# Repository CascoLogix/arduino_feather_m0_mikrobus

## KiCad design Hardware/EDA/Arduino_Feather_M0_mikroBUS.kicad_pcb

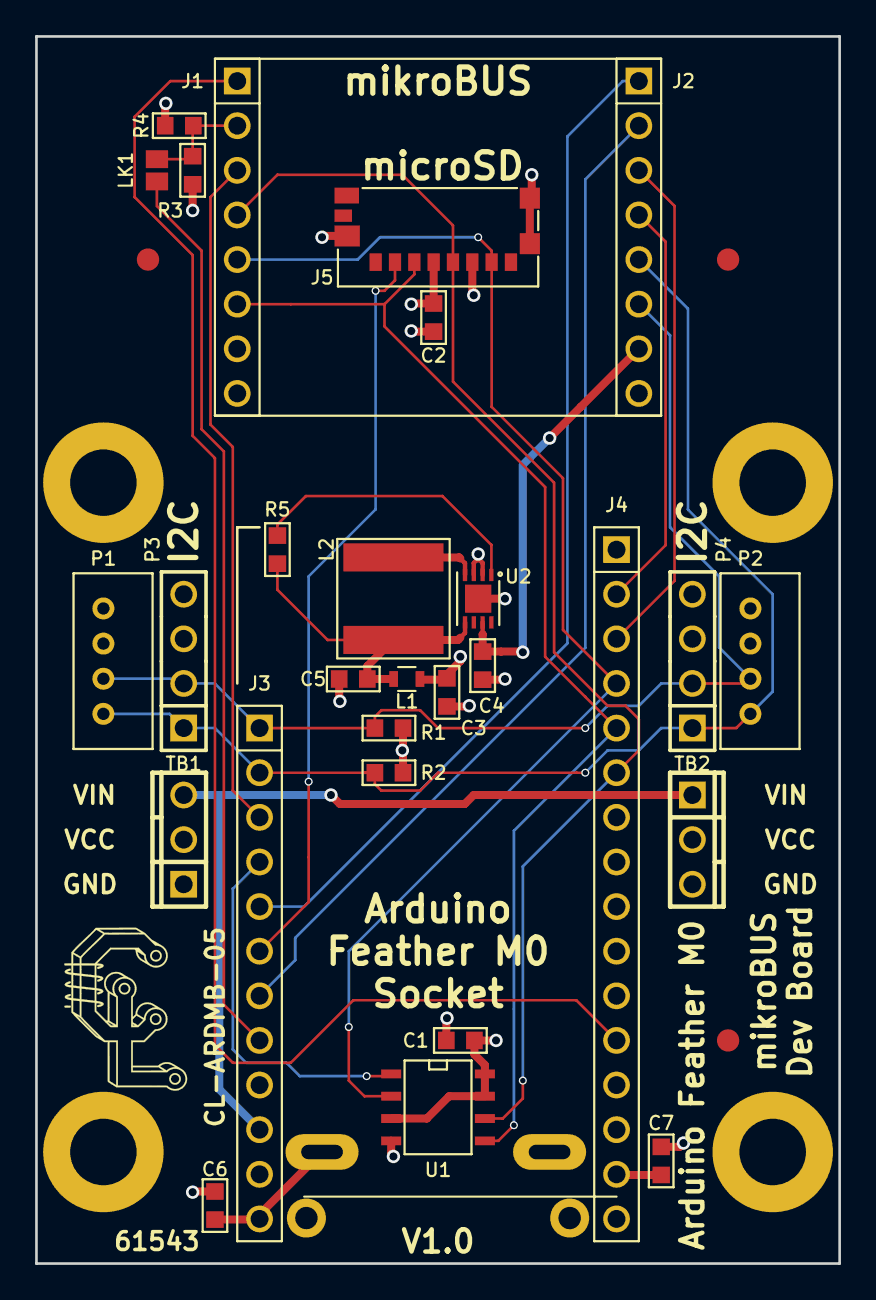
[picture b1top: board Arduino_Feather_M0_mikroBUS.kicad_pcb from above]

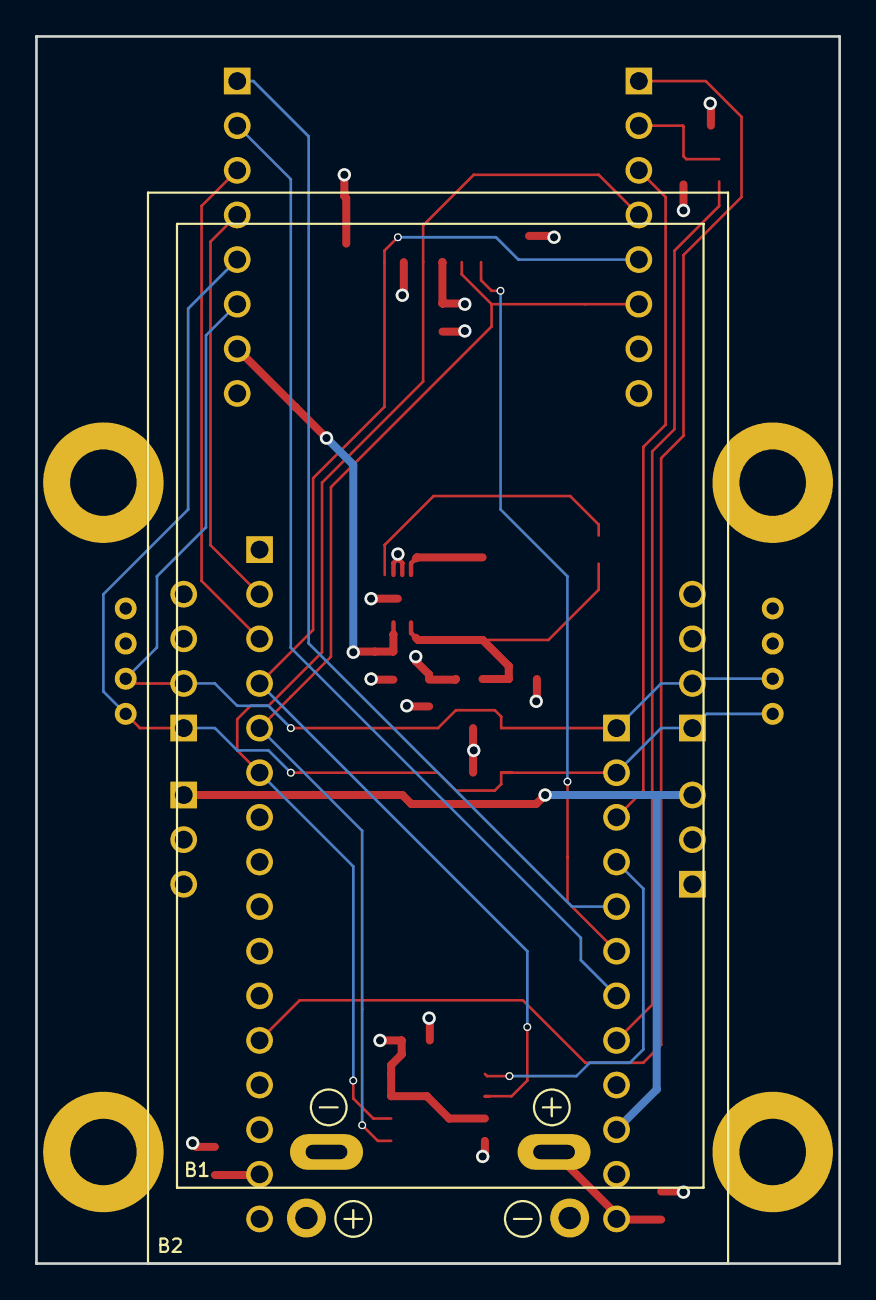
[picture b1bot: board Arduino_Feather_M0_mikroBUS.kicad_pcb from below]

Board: 4 copper layers, 45.7 x 69.8 mm, 38 parts (2 on the bottom side), 23 nets.

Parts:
B1: 9V; BC9VPC
B2: 2xAA; Keystone_2462_2AA
C1, C2, C3, C7: 0.1uF; 0603
C4, C5, C6: 10uF; 0603
G1: Casco_Logix_Logo; Casco_Logix_Logo_7x7MM
J1, J2: HEADER_F_2.54MM_1R8P_ST_AU_PTH
J3: HEADER_F_2.54MM_1R12P_ST_AU_PTH
J4: Val**; HEADER_F_2.54MM_1R16P_ST_AU_PTH
J5: Molex_0475710001
L1: F_Bead; L_0603
L2: 4.7uH; DG6050C
LK1: SOLDER_LINK_NO
M1, M2, M3: FID; FIDUCIAL
MH1, MH2, MH3, MH4: MTG_HOLE; MH_#6
P1, P2: HEADER_M_2.54MM_1R4P_ST_AU_PTH; PH_2.0_PTH
P3, P4: HEADER_M_2.54MM_1R4P_ST_AU_PTH
R1, R2, R5: 4.7k; R0603
R3, R4: DNP; R0603
TB1, TB2: OSTVN_1x3; TB_100MIL_1R3P_PTH
U1: FL127; SO-8
U2: DIO6605B; DFN2-3-8

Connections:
5.0V: C4.1, J2.7, U2.7
+3V3: B2.1, C1.1, C2.1, C3.1, C7.1, J1.7, J4.15, J5.4, L1.1, P1.3, P2.3, P3.3, P4.3, R1.1, R2.1, R3.1, TB1.2, TB2.2, U1.3, U1.7, U1.8
/DIO_SW: L2.2, U2.4
/DIO_VIN: C5.1, L1.2, L2.1, R5.2, U2.5
A0: J1.1, J4.12
D5: J1.3, J3.3
D6: J3.4, U1.1
D9: J2.1, J3.5
D10: J3.6, J5.2
D11: J2.2, J3.7
D12: J3.8, LK1.1
GND: B1.2, B2.2, C1.2, C2.2, C3.2, C4.2, C5.2, C6.2, C7.2, J1.8, J2.8, J4.1, J4.13, J5.6, J5.9, J5.10, J5.11, MH1.~, MH2.~, MH3.~, MH4.~, P1.4, P2.4, P3.4, P4.4, R4.2, TB1.1, TB2.3, U1.4, U2.2, U2.3, U2.9
MISO: J1.5, J4.4, J5.7, U1.2
MOSI: J1.6, J4.5, J5.3, U1.5
unnamed: J1.2, LK1.2, R3.2, R4.1
unnamed: R5.1, U2.1
RXD: J2.3, J4.3
SCK: J1.4, J4.6, J5.5, U1.6
SCL: J2.5, J3.2, P1.1, P2.1, P3.1, P4.1, R2.2
SDA: J2.6, J3.1, P1.2, P2.2, P3.2, P4.2, R1.2
TXD: J2.4, J4.2
VBAT: B1.1, C6.1, J3.12
VIN: J3.10, TB1.3, TB2.1

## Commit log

2017-12-29 Initial commit.
2017-12-29 Updated title block info and PCB silkscreen artwork.
2020-02-01 Updated to KiCAD 5.1.5 and remapped schematic symbols.
2020-02-01 Updated title blocks and made header pin assignments for Arduino Feather M0.
2020-02-02 Updated schematic with pin assignments of feather M0 and 5V DC-DC boost power supply. Updated PCB with feather M0 headers and all routing complete. Few tweaks remain per notes on layout.
2020-02-03 Updated footprints for B1 and B2. Shifted headers for feather M0 down to allow more room for feather M0 near mikroBUS socket.
2020-02-03 Added step file for Adafruit feather M0 to board model.
2020-02-25 Updated headers, added power supply, increased board height slightly.
